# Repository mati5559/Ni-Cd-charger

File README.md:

# Ni-Cd charger
Charger for 24V (10 s) NiCd battery

# Description
This charger was designed to charge 24V NiCd battery with current about 1,2A. It uses continous current method and delta V detection. 

Schematic contains DC-DC step up converter, microcontroller, current source.
Step up converter generates higher voltage than input voltage and limits current. It is very efficient (about 85%).
Current source limits short circuit current and charging current when battery voltage is lower than input voltage. It generates a lot of heat, so it have big radiator and temperature sensor to prevent overheat. In case of overheat charging will be interrupted  and error LED will blink. After cooling down charging will be resumed automatically. Current source works only for a while at the beginning of charging and when circuit is shorted. Most of the time it is turned off and do not generate heat. 
Microcontroller controls charging process, turns on and off step up converter and current source, measures voltages, tepmerature etc. 

You can regulate charging current with R13 potentiometer, short circuit current with R6 potentiometer (it must be greather than charging current) and maximum output voltage with R16 potentiometer. 

Other parameters can be modified in config.hpp file before programming Attiny13. 

# How to use it
1. Connect power supply to X1 screw clamp (20V 4A).
2. Connect battery to X2 screw clamp and temperature sensor to pin 3 and 4 of JP1. (short pin 3 and 4 of JP1 if your battery do not have temperature sensor)
3. LED1 should light up.
4. Charging is ended when both LEDs are not lighting.

If LED2 is blinking it seems that over temperature protection was activated. You should wait a while to cool down. Charger will automatically turn on.
If LED2 lights constantly it seems that something went wrong (for example battery was disconnected, is dead or charger is broken). You should turn off power supply for a while, make sure that all is connected properly and turn on power supply. 

GNU GPL license
Source code and hardware is open and free of charge for everyone.

Author is not responsible for any damages made by this device.
You make and use it at your own risk.

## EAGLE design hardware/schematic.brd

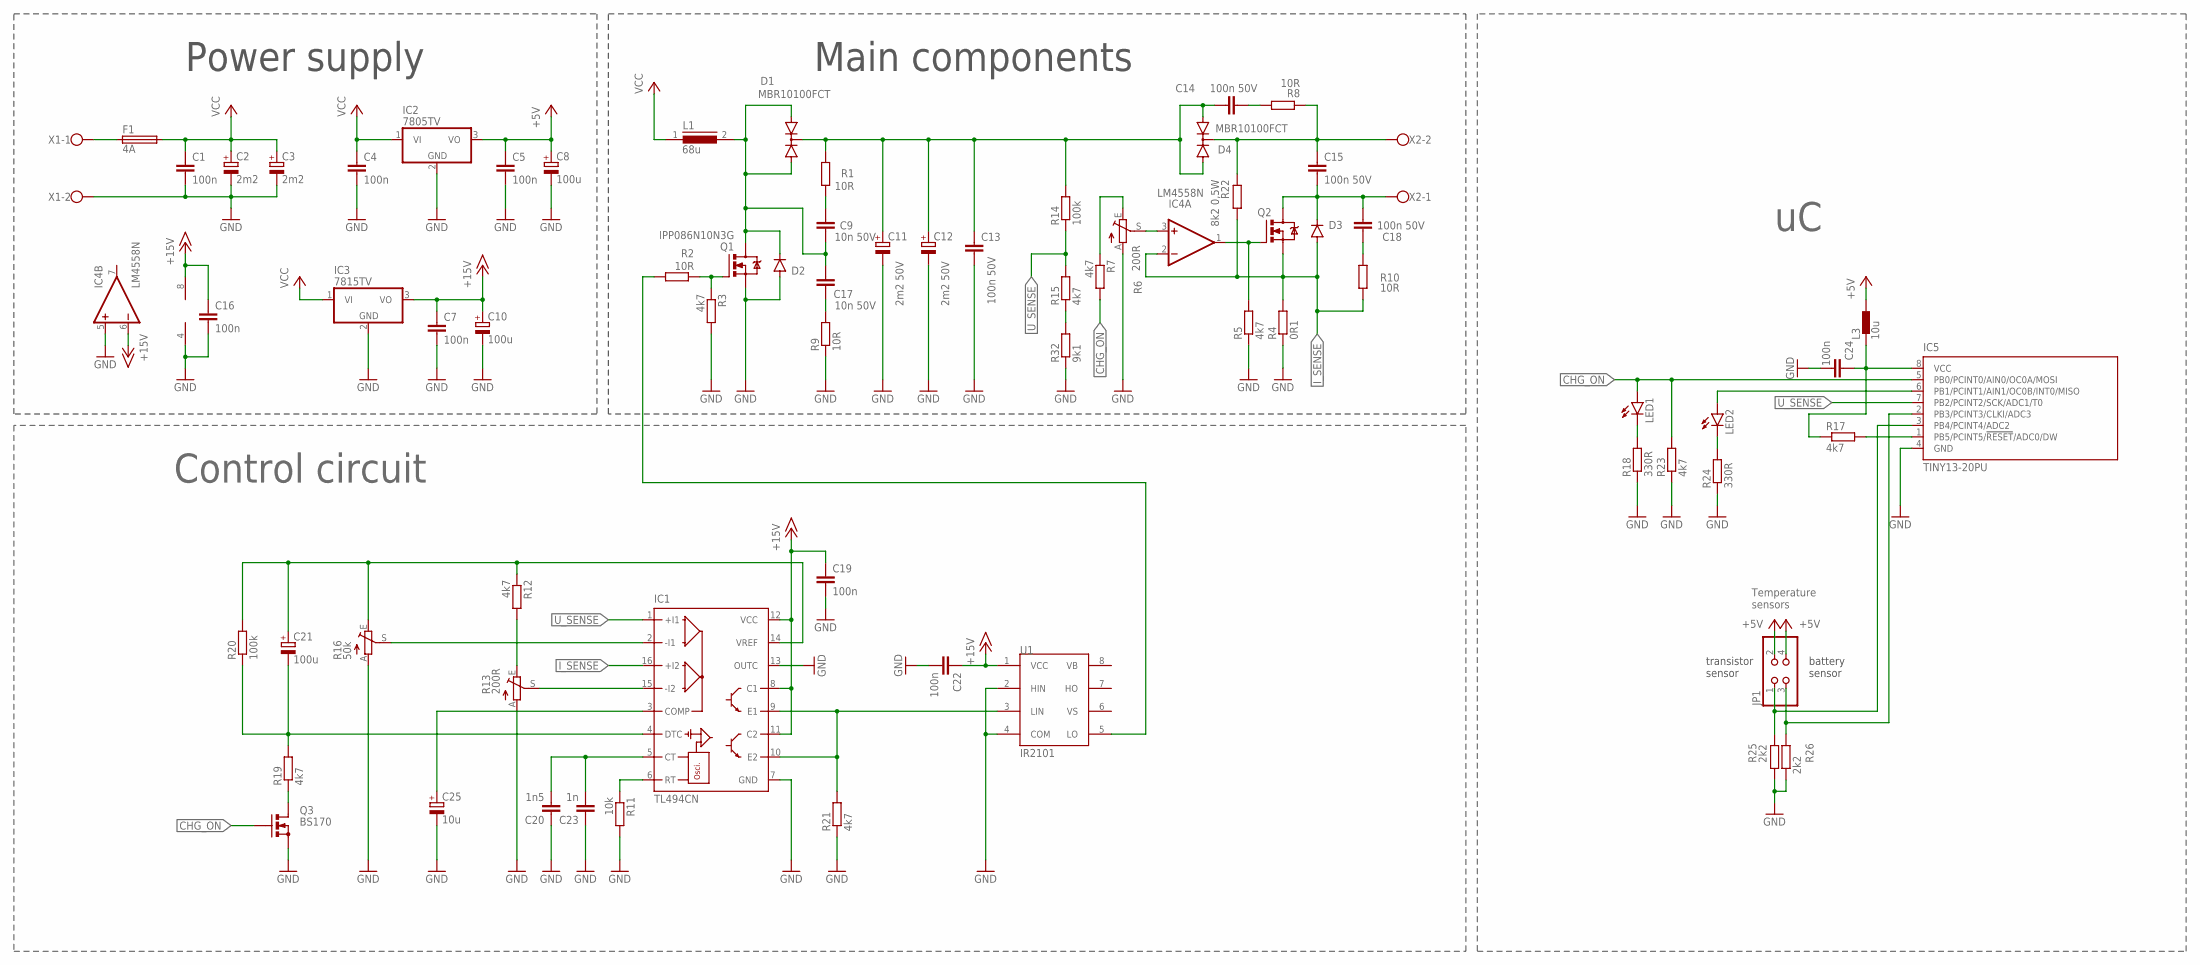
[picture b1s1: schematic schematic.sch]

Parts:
C1, C4, C5, C7, C16, C19, C22, C24: 100n; C2.5-2
C2, C3: 2m2; E7,5-16
C8, C10, C21: 100u; E3,5-8
C9, C17: 10n 50V; C2.5-2
C11, C12: 2m2 50V; E7,5-18
C13, C14, C15, C18: 100n 50V; C2.5-2
C20: 1n5; C2.5-2
C23: 1n; C2.5-2
C25: 10u; E2,5-5
D1, D4: MBR10100FCT; TO220ABS
D2, D3: 1N4933; DO41-10
F1: 4A; SH22
IC1: TL494CN; DIL16
IC2: 7805TV; TO220V
IC3: 7815TV; TO220V
IC4: LM4558N; DIL08
IC5: TINY13-20PU; DIL08
JP1: PINHD-2X2; 2X02
L1: 68u; SFT1240
L3: 10u; BL01RN1A
LED1, LED2: LED5MM
Q1: IPP086N10N3G; TO220BV
Q2: IRF520; TO220BV
Q3: BS170; SOT54E
R1, R2, R8, R9, R10: 10R; 0204/7
R3, R5, R7, R12, R15, R17, R19, R21, R23: 4k7; 0204/7
R4: 0R1; 0204/5
R6, R13: 200R; B64Y
R11: 10k; 0204/7
R14, R20: 100k; 0204/7
R16: 50k; B64W
R18, R24: 330R; 0204/7
R22: 8k2 0,5W; 0204/7
R25, R26: 2k2; 0204/7
R32: 9k1; 0204/7
U1: IR2101; DIL08
X1, X2: W237-102

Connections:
+5V: C5.1, C8.+, IC2.3 (VO), JP1.2, JP1.4, L3.2
+15V: C7.1, C10.+, C16.1, C19.1, C22.1, IC1.8 (C1), IC1.11 (C2), IC1.12 (VCC), IC3.3 (VO), IC4.6 (-IN), IC4.8 (V+), U1.1 (VCC)
CHG_ON: IC5.5 (PB0/PCINT0/AIN0/OC0A/MOSI), LED1.A, Q3.G, R7.2, R23.2
GND: C1.2, C2.-, C3.-, C4.2, C5.2, C7.2, C8.-, C10.-, C11.-, C12.-, C13.2, C16.2, C19.2, C20.1, C22.2, C23.1, C24.2, C25.-, D2.A, IC1.7 (GND), IC1.13 (OUTC), IC2.2 (GND), IC3.2 (GND), IC4.4 (V-), IC4.5 (+IN), IC5.4 (GND), Q1.S, Q3.S, R3.2, R4.1, R5.1, R6.A, R9.1, R11.2, R13.A, R16.A, R18.1, R21.1, R23.1, R24.1, R25.1, R26.1, R32.1, U1.2 (HIN), U1.4 (COM), X1.2
I_SENSE: D3.A, IC1.16 (+I2), IC4.2 (-IN), Q2.S, R4.2, R10.2, R22.2
unnamed: F1.1, X1.1
unnamed: C18.2, R10.1
unnamed: C11.+, C12.+, C13.1, C14.2, D1.C, D4.A1, D4.A2, R1.2, R14.2
unnamed: Q1.G, R2.1, R3.1
unnamed: C17.2, R9.2
unnamed: IC1.15 (-I2), R13.S
unnamed: C15.2, C18.1, D3.C, Q2.D, X2.1
unnamed: IC4.1 (OUT), Q2.G, R5.2
unnamed: R6.E, R7.1
unnamed: IC4.3 (+IN), R6.S
unnamed: C14.1, R8.2
unnamed: C15.1, D4.C, R8.1, R22.1, X2.2
unnamed: C9.2, C17.1, D1.A1, D1.A2, D2.C, L1.2, Q1.D
unnamed: C9.1, R1.1
unnamed: C20.2, C23.2, IC1.5 (CT)
unnamed: IC1.6 (RT), R11.1
unnamed: R12.2, R13.E
unnamed: C21.+, IC1.14 (VREF), R12.1, R16.E, R20.2
unnamed: IC1.2 (-I1), R16.S
unnamed: LED2.K (C), R24.2
unnamed: IC5.1 (PB5/PCINT5/!RESET!/ADC0/DW), R17.2
unnamed: Q3.D, R19.1
unnamed: C21.-, IC1.4 (DTC), R19.2, R20.1
unnamed: IC1.9 (E1), IC1.10 (E2), R21.2, U1.3 (LIN)
unnamed: R2.2, U1.5 (LO)
unnamed: LED1.K (C), R18.2
unnamed: C25.+, IC1.3 (COMP)
unnamed: C24.1, IC5.8 (VCC), L3.1, R17.1
unnamed: IC5.6 (PB1/PCINT1/AIN1/OC0B/INT0/MISO), LED2.A
unnamed: IC5.3 (PB4/PCINT4/ADC2), JP1.1, R25.2
unnamed: IC5.2 (PB3/PCINT3/CLKI/ADC3), JP1.3, R26.2
unnamed: R15.1, R32.2
U_SENSE: IC1.1 (+I1), IC5.7 (PB2/PCINT2/SCK/ADC1/T0), R14.1, R15.2
VCC: C1.1, C2.+, C3.+, C4.1, F1.2, IC2.1 (VI), IC3.1 (VI), L1.1

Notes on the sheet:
Power supply
Main components
transistor sensor
battery sensor
Temperature sensors
Control circuit

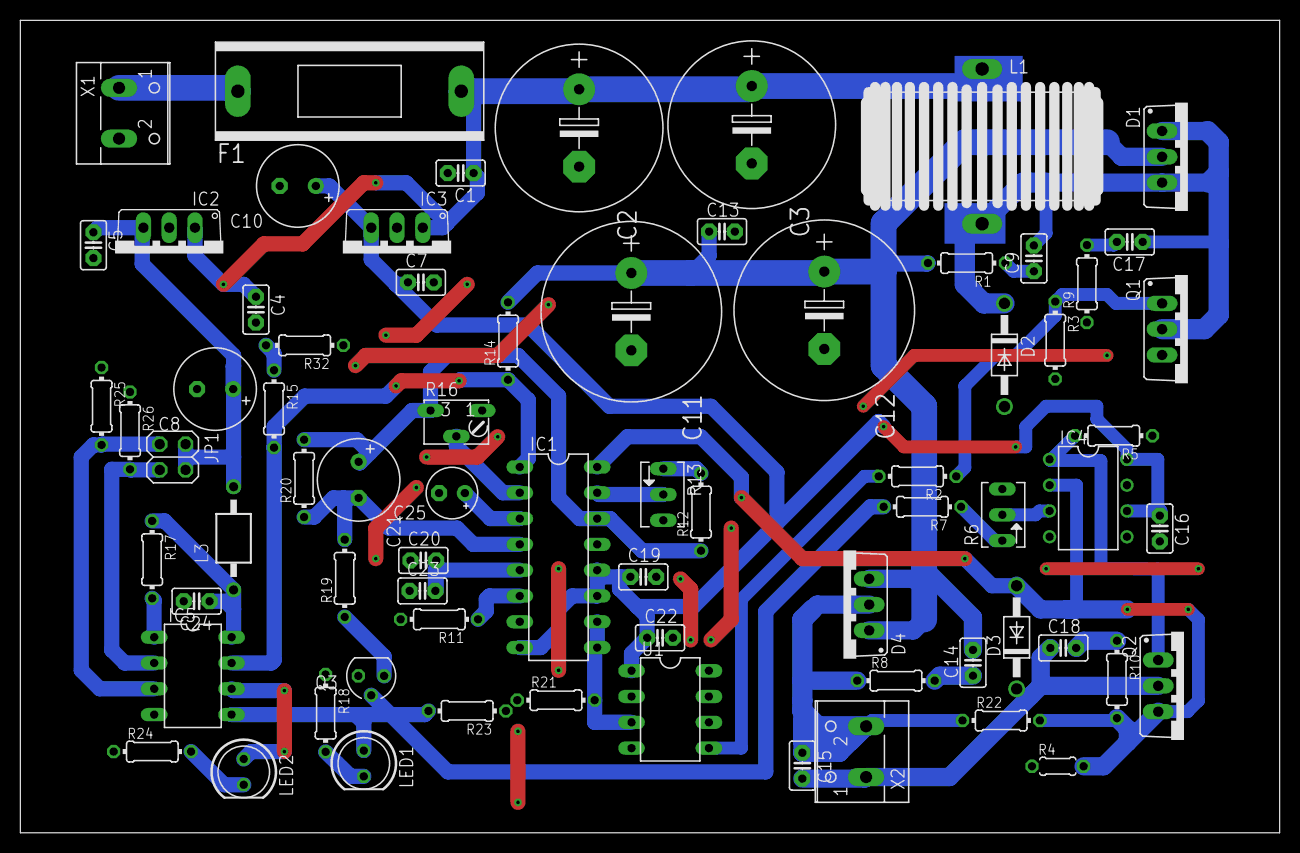
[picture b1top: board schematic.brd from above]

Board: 2 copper layers, 124.0 x 80.0 mm, 72 parts (0 on the bottom side), 39 nets.

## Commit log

2022-05-05 Improved working of ADC, added some other small changes

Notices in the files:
parts and their libraries:
irf-2: Copyright & License
This library is licensed under the General Public License, Version 2.
More Information about the General Public License is available at http://www.gnu.org/copyleft/gpl.html.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
